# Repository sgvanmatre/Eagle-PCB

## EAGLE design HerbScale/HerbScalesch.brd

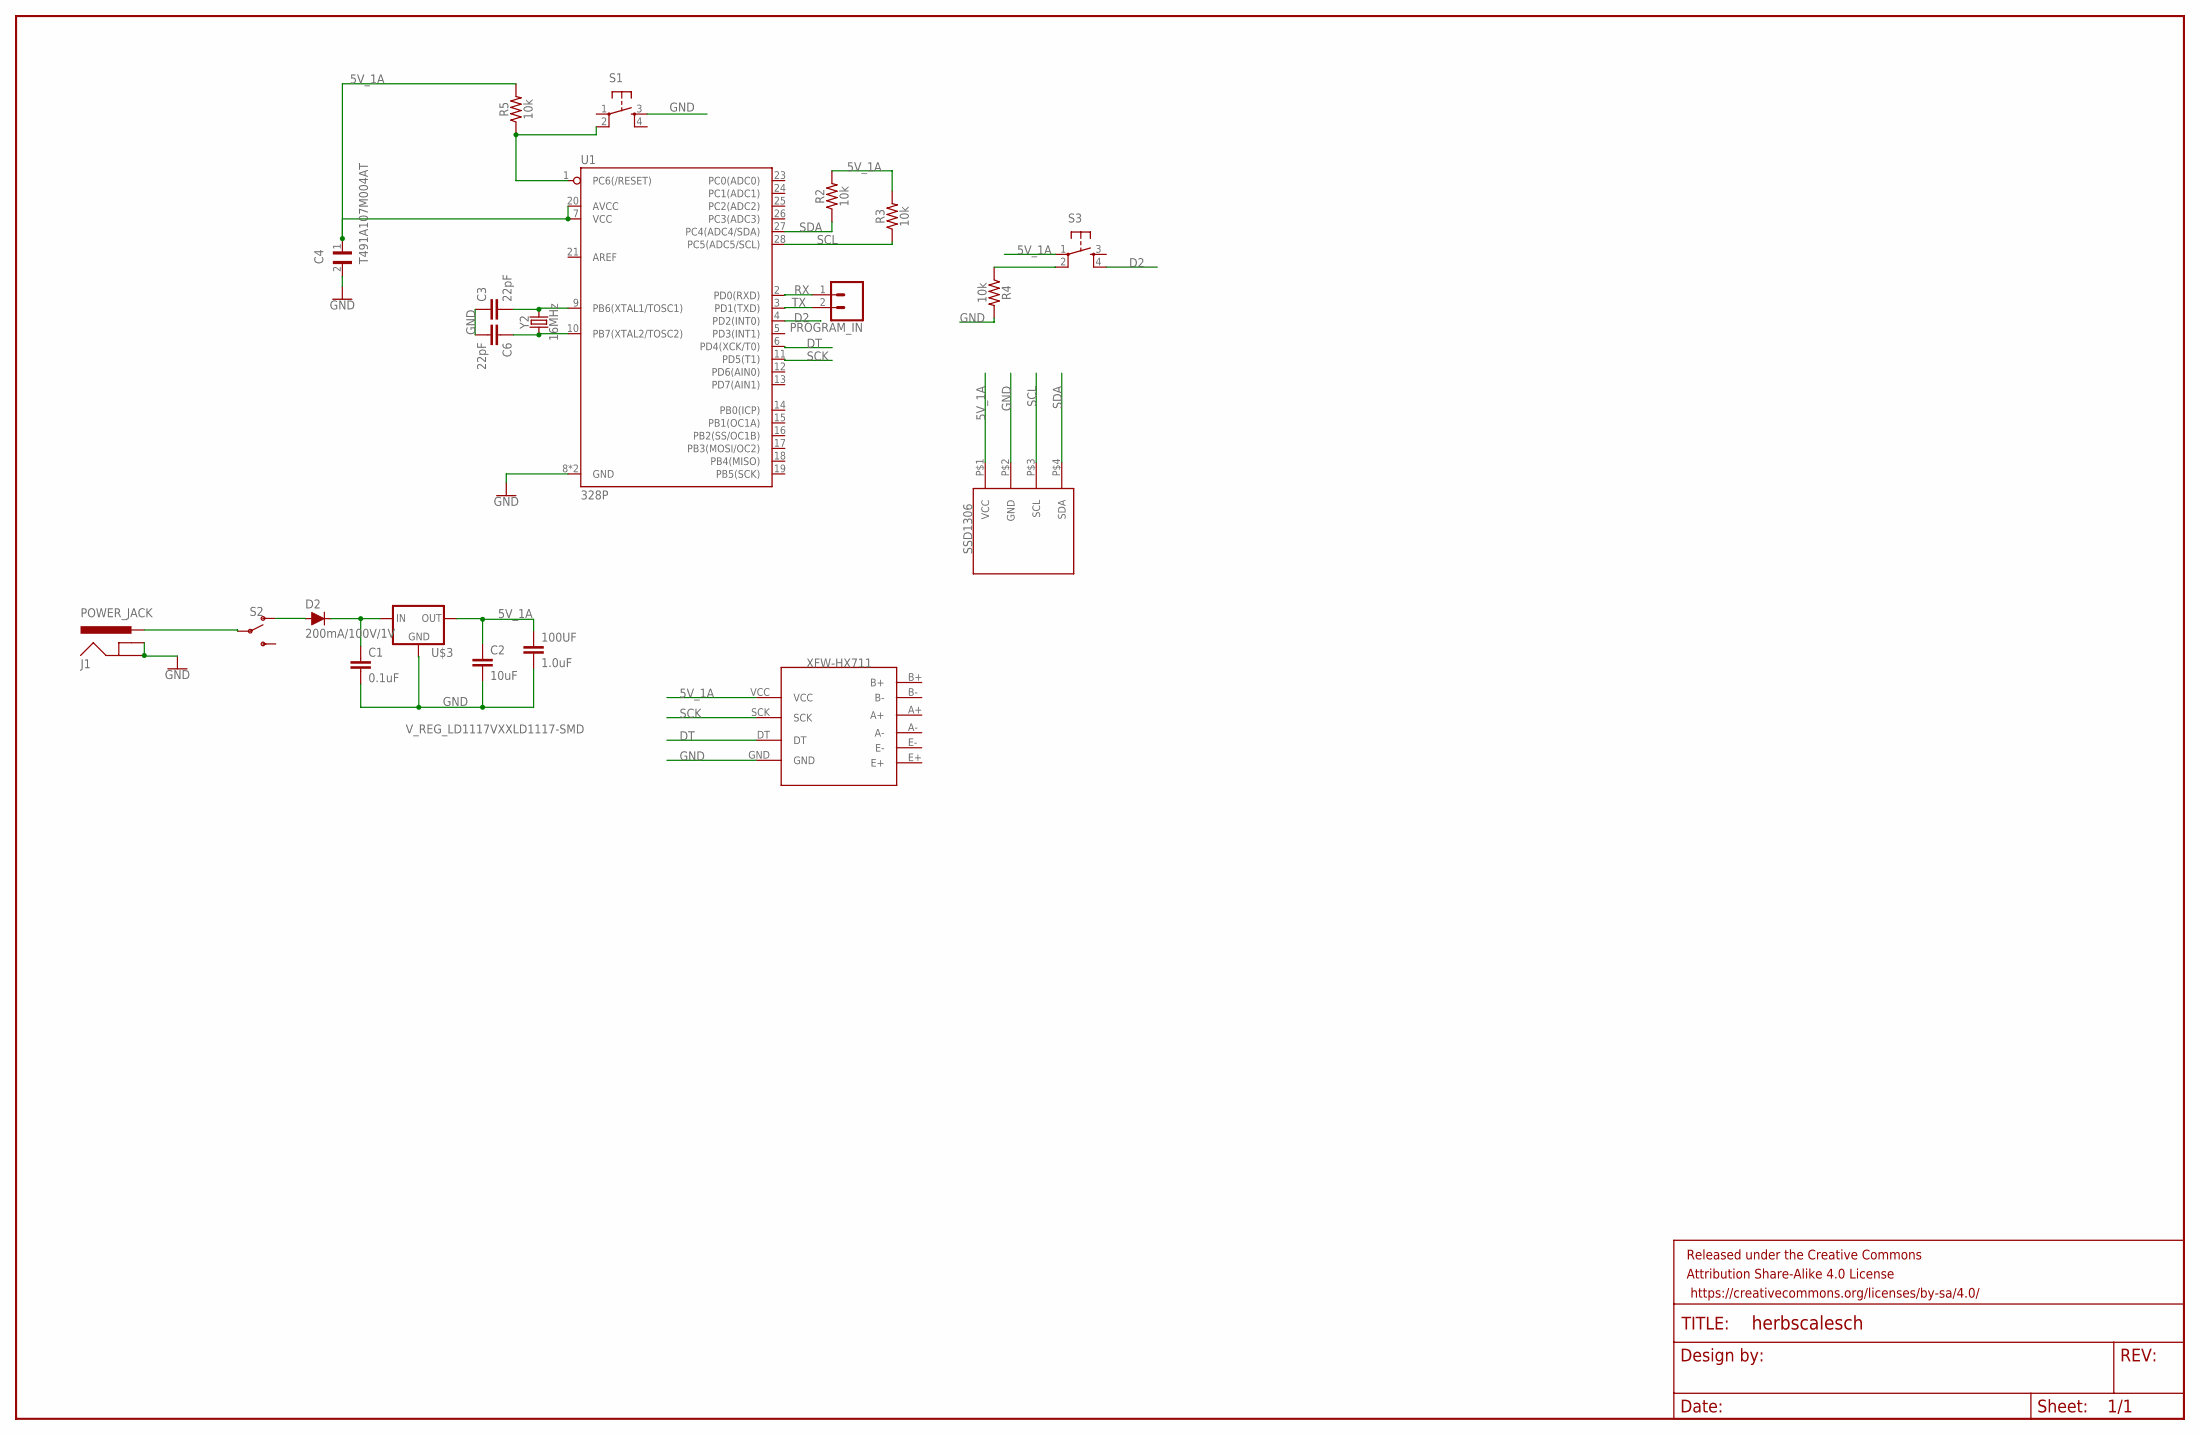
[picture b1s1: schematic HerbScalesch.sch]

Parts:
100UF: 1.0uF; 1206
C1: 0.1uF; 0603
C2: 10uF; 0603
C3, C6: 22pF; CAP-PTH-2.54
C4: T491A107M004AT; CAPC3216X110N
D2: 200mA/100V/1V; DIODE-1N4148
FRAME1: FRAME-LEDGER; CREATIVE_COMMONS
J1: POWER_JACK; POWER_JACK_PTH
PROGRAM_IN: CONN_02; 1X02
R2, R3, R4, R5: 10k; AXIAL-0.3
S1, S3: TAC_SWITCHPTH; TACTILE-PTH
S2: SWITCH-SPDT-PTH-11.6X4.0MM; SWITCH_SPDT_PTH_11.6X4.0MM
U1: 328P; DIP28
U$1: SSD1306
U$2: XFW-HX711
U$3: V_REG_LD1117VXXLD1117-SMD; SOT223
Y2: 16MHz; HC49US

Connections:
5V_1A: 100UF.1, C2.1, C4.1, R2.P$2 (2), R3.P$2 (2), R5.P$2 (2), S3.1, U1.7 (VCC), U1.20 (AVCC), U$1.P$1 (VCC), U$2.VCC, U$3.2 (OUT)
D2: S3.4, U1.4 (PD2(INT0))
DT: U1.6 (PD4(XCK/T0)), U$2.DT
GND: 100UF.2, C1.2, C2.2, C3.1, C4.2, C6.2, J1.GND, J1.GNDBREAK, R4.P$2 (2), S1.3, U1.8 (GND), U1.22 (GND), U$1.P$2 (GND), U$2.GND, U$3.1 (GND)
unnamed: C3.2, U1.9 (PB6(XTAL1/TOSC1)), Y2.2
unnamed: R5.P$1 (1), S1.2, U1.1 (PC6(/RESET))
unnamed: D2.A, S2.1 (O)
unnamed: C1.1, D2.C, U$3.3 (IN)
unnamed: C6.1, U1.10 (PB7(XTAL2/TOSC2)), Y2.1
unnamed: R4.P$1 (1), S3.2
unnamed: J1.PWR, S2.2
RX: PROGRAM_IN.1, U1.2 (PD0(RXD))
SCK: U1.11 (PD5(T1)), U$2.SCK
SCL: R3.P$1 (1), U1.28 (PC5(ADC5/SCL)), U$1.P$3 (SCL)
SDA: R2.P$1 (1), U1.27 (PC4(ADC4/SDA)), U$1.P$4 (SDA)
TX: PROGRAM_IN.2, U1.3 (PD1(TXD))

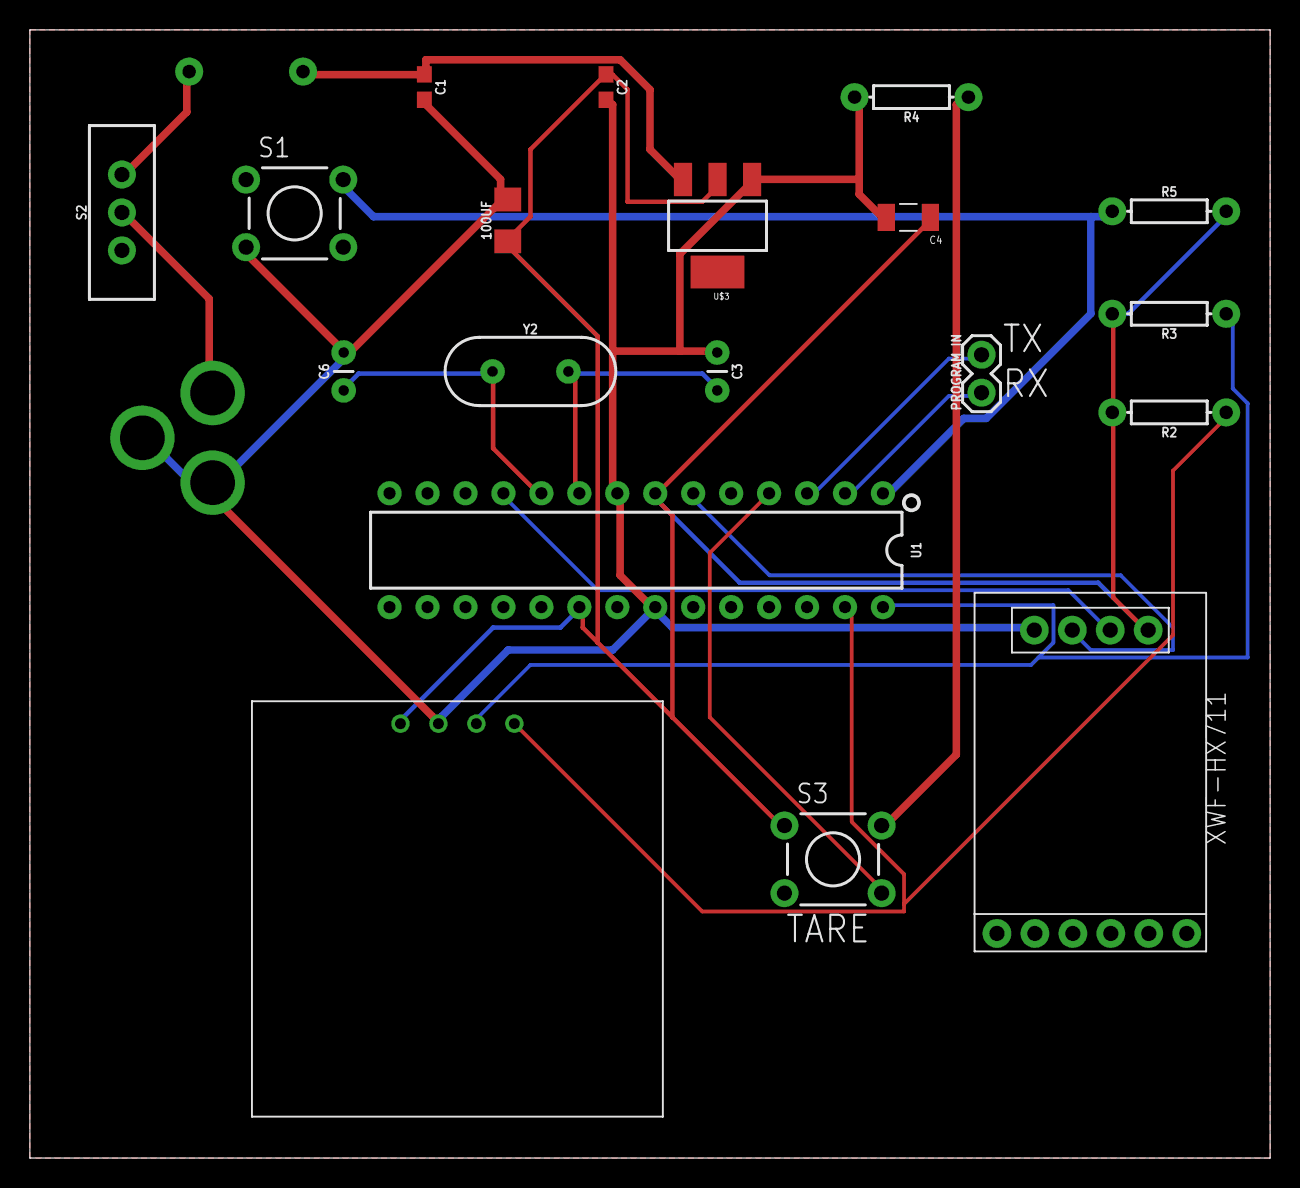
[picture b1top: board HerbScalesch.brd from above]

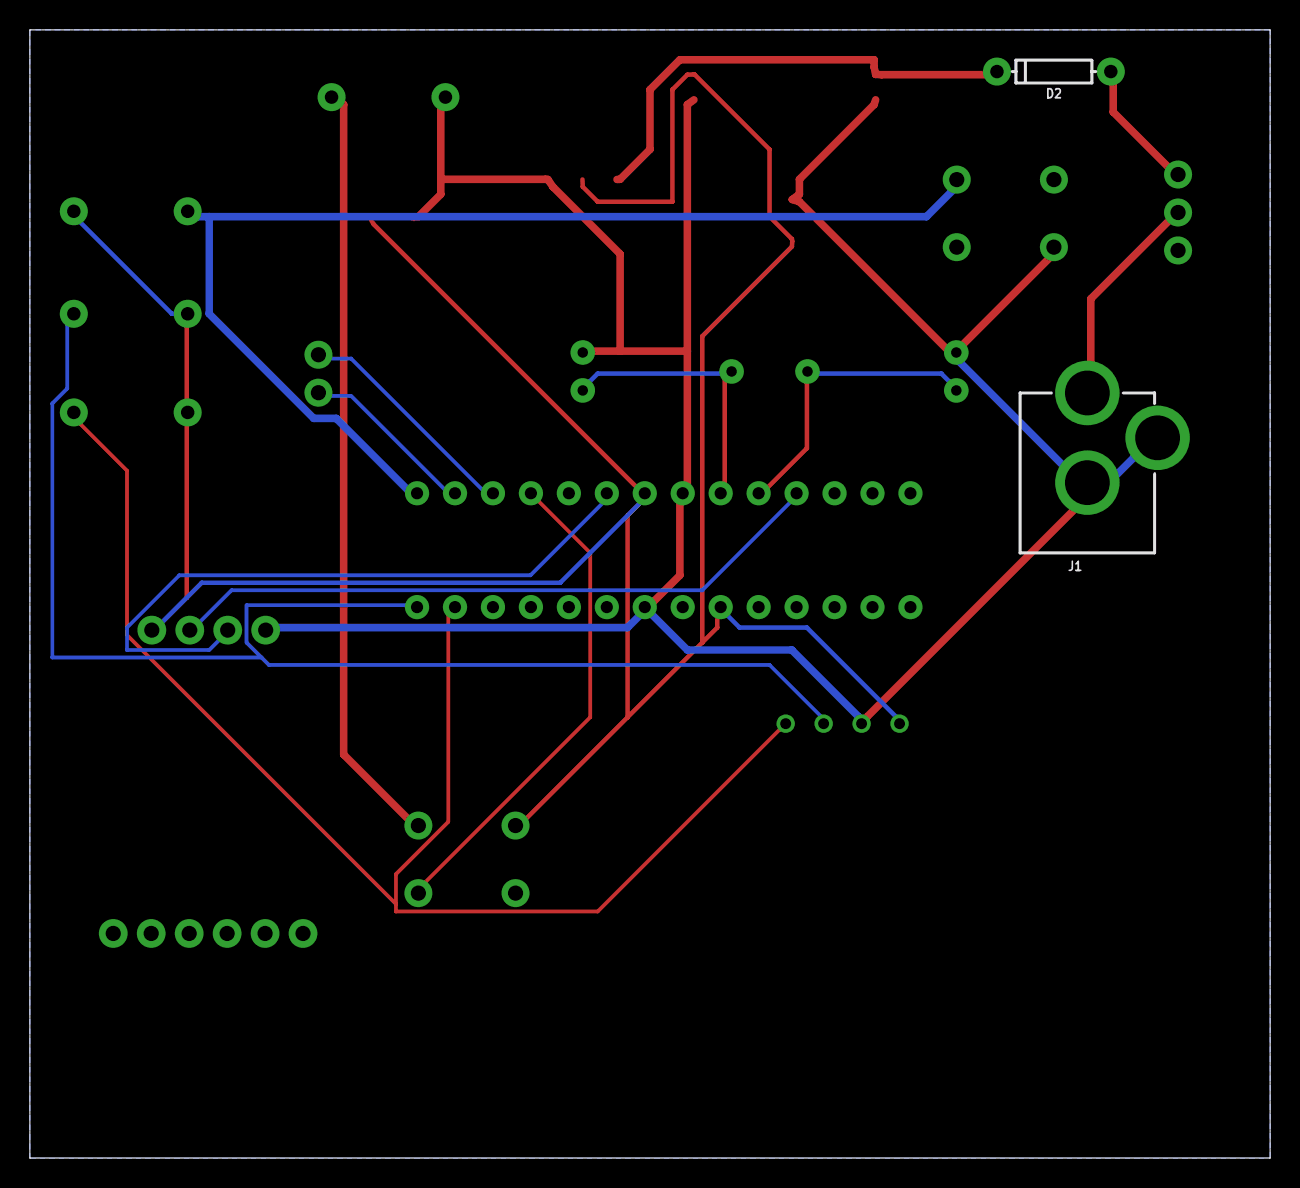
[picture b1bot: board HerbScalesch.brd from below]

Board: 2 copper layers, 83.0 x 75.5 mm, 22 parts (2 on the bottom side), 16 nets.

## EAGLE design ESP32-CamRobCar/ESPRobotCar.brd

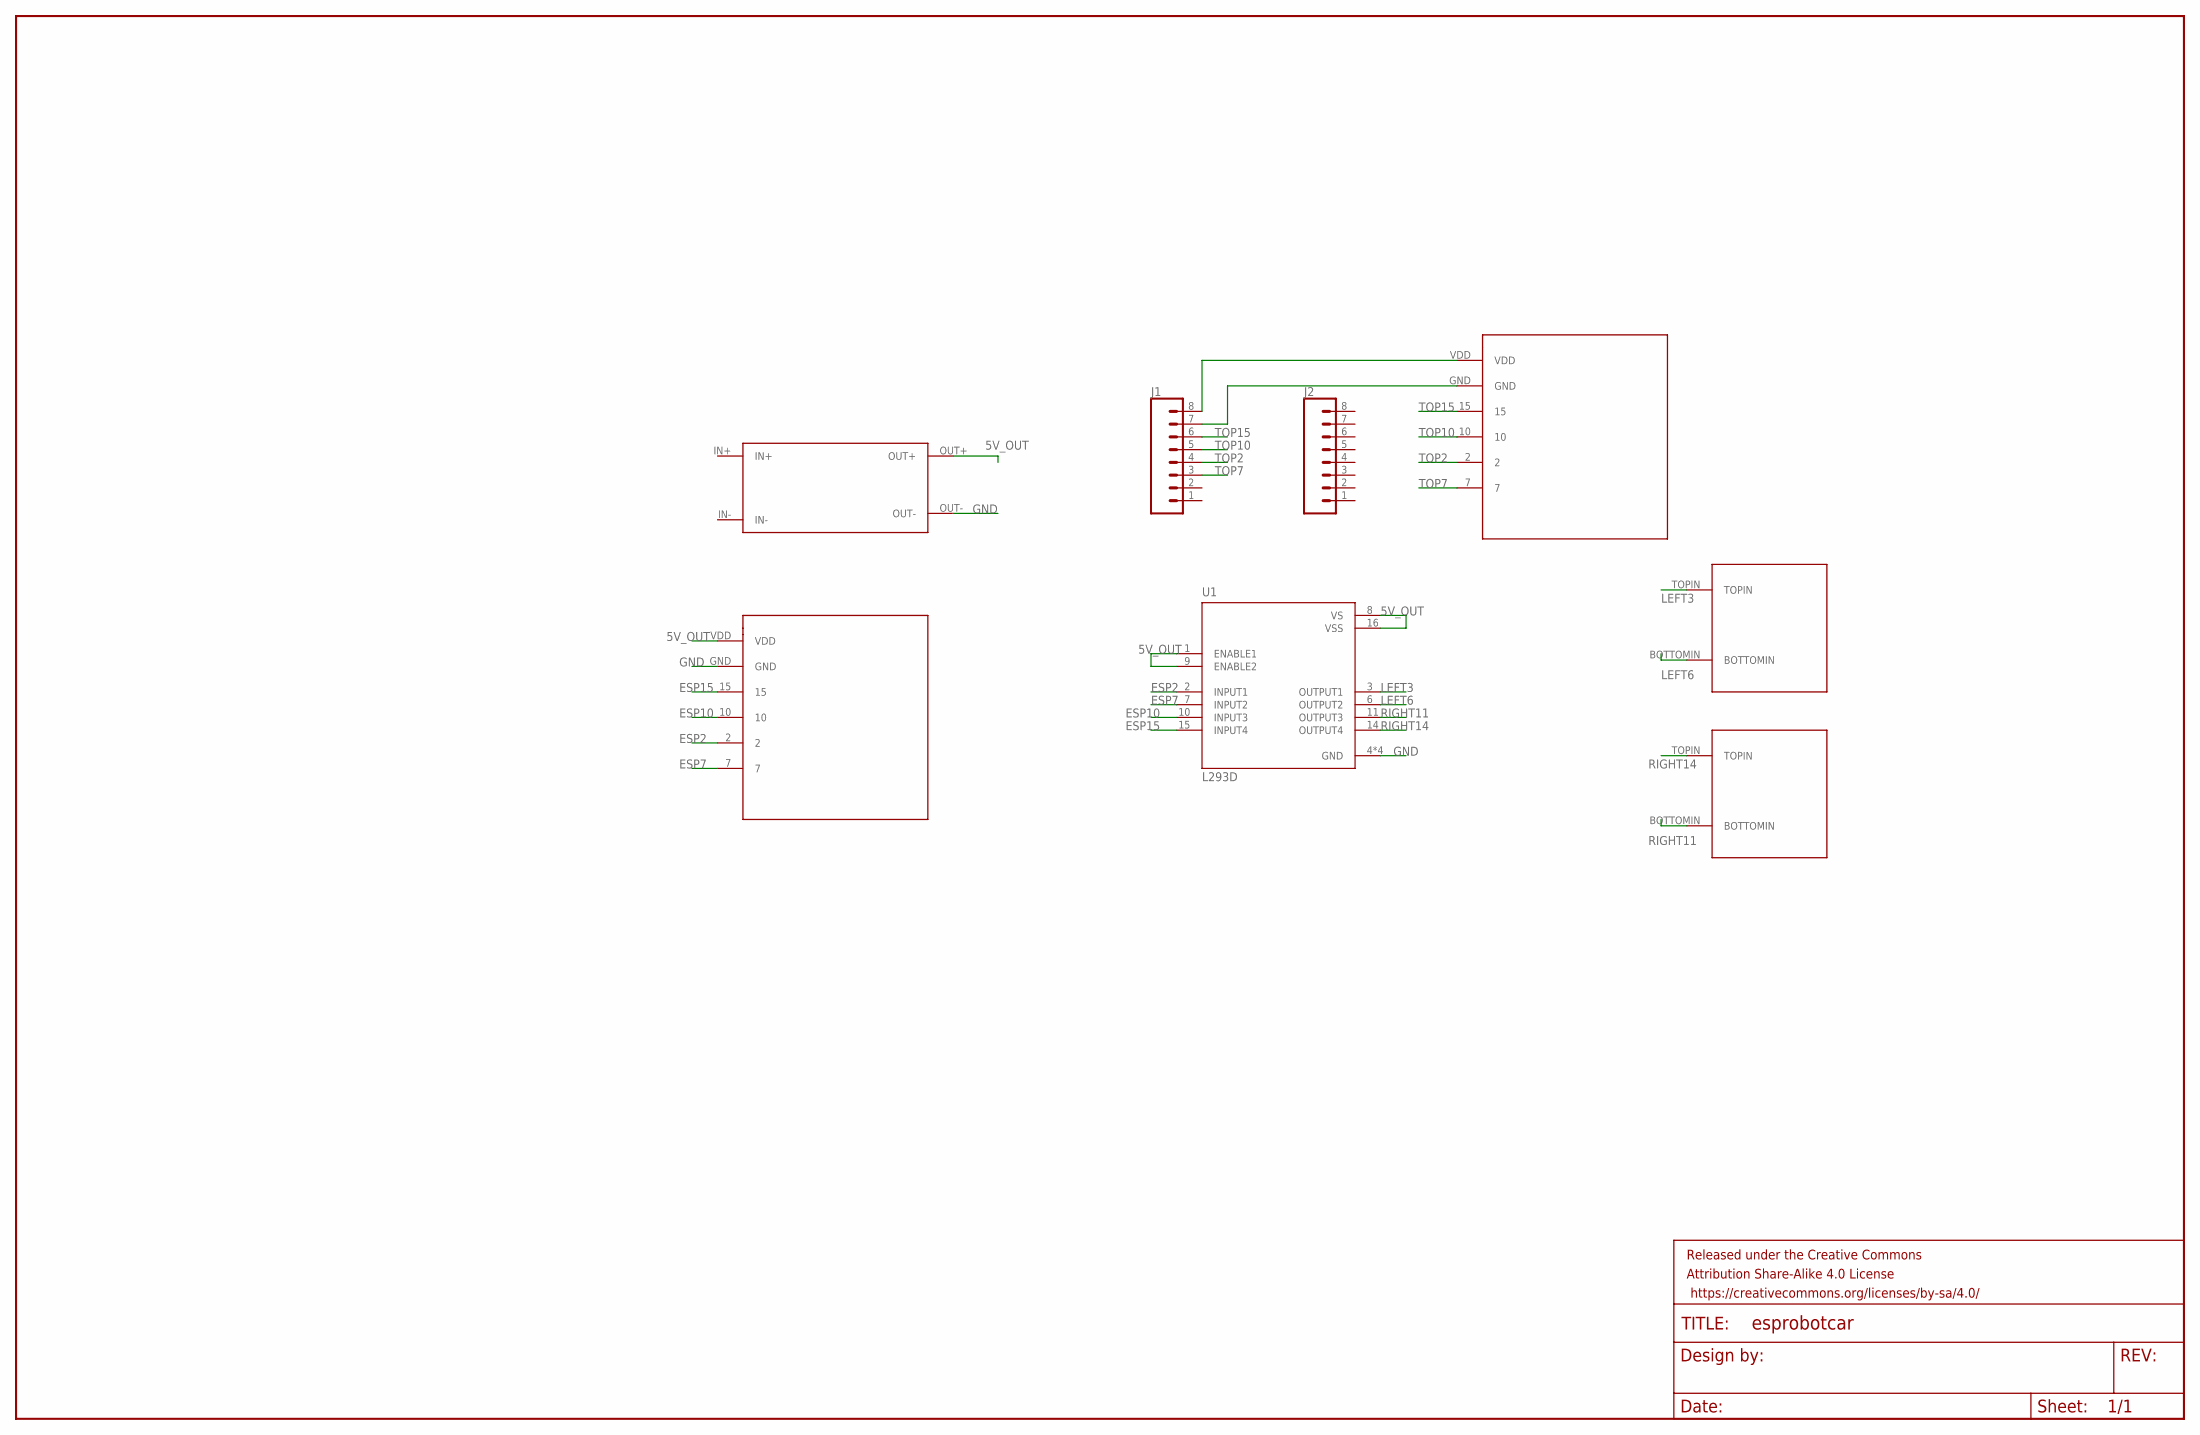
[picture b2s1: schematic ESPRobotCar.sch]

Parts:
FRAME1: FRAME-LEDGER; CREATIVE_COMMONS
J1, J2: CONN_08"; 1X08
U1: L293D; DIP880W50P254L2000H510Q16
U$1: DC_TO_DC; DCTODC
U$2, U$3: MOTORPAD
U$4, U$5: MOTORBREAK

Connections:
5V_OUT: U1.1 (ENABLE1), U1.8 (VS), U1.9 (ENABLE2), U1.16 (VSS), U$1.OUT+, U$4.VDD
ESP2: U1.2 (INPUT1), U$4.2
ESP7: U1.7 (INPUT2), U$4.7
ESP10: U1.10 (INPUT3), U$4.10
ESP15: U1.15 (INPUT4), U$4.15
GND: U1.4 (GND), U1.5 (GND), U1.12 (GND), U1.13 (GND), U$1.OUT-, U$4.GND
LEFT3: U1.3 (OUTPUT1), U$2.TOPIN
LEFT6: U1.6 (OUTPUT2), U$2.BOTTOMIN
unnamed: J1.8, U$5.VDD
unnamed: J1.7, U$5.GND
RIGHT11: U1.11 (OUTPUT3), U$3.BOTTOMIN
RIGHT14: U1.14 (OUTPUT4), U$3.TOPIN
TOP2: J1.4, U$5.2
TOP7: J1.3, U$5.7
TOP10: J1.5, U$5.10
TOP15: J1.6, U$5.15

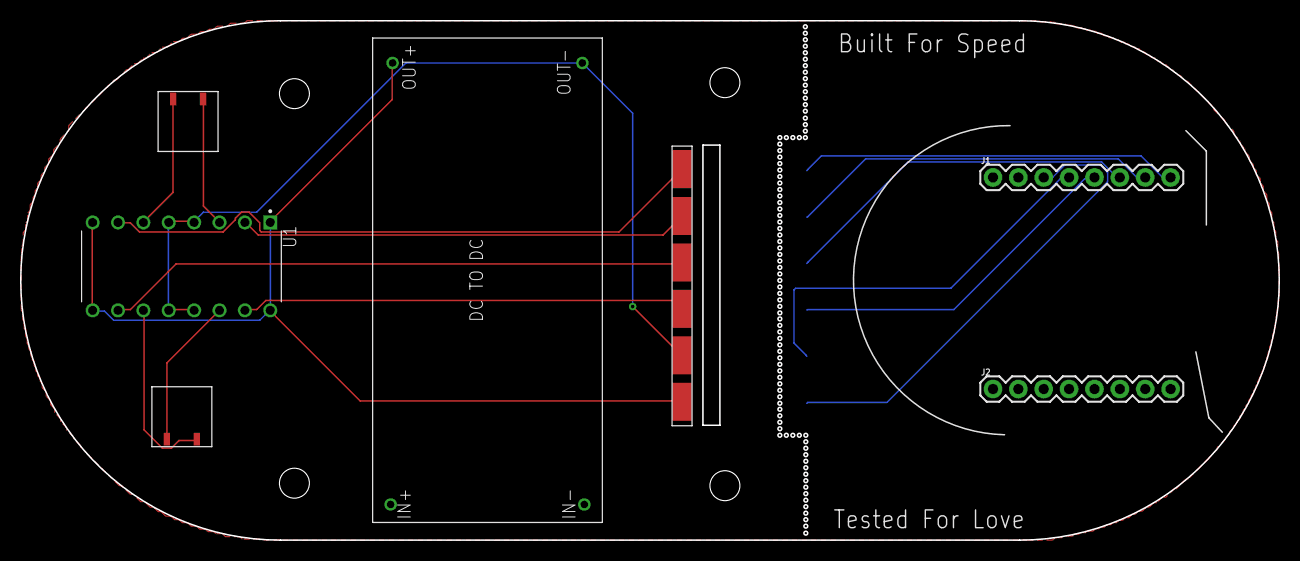
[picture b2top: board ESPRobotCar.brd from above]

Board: 2 copper layers, 126.0 x 52.0 mm, 9 parts (1 on the bottom side), 16 nets.

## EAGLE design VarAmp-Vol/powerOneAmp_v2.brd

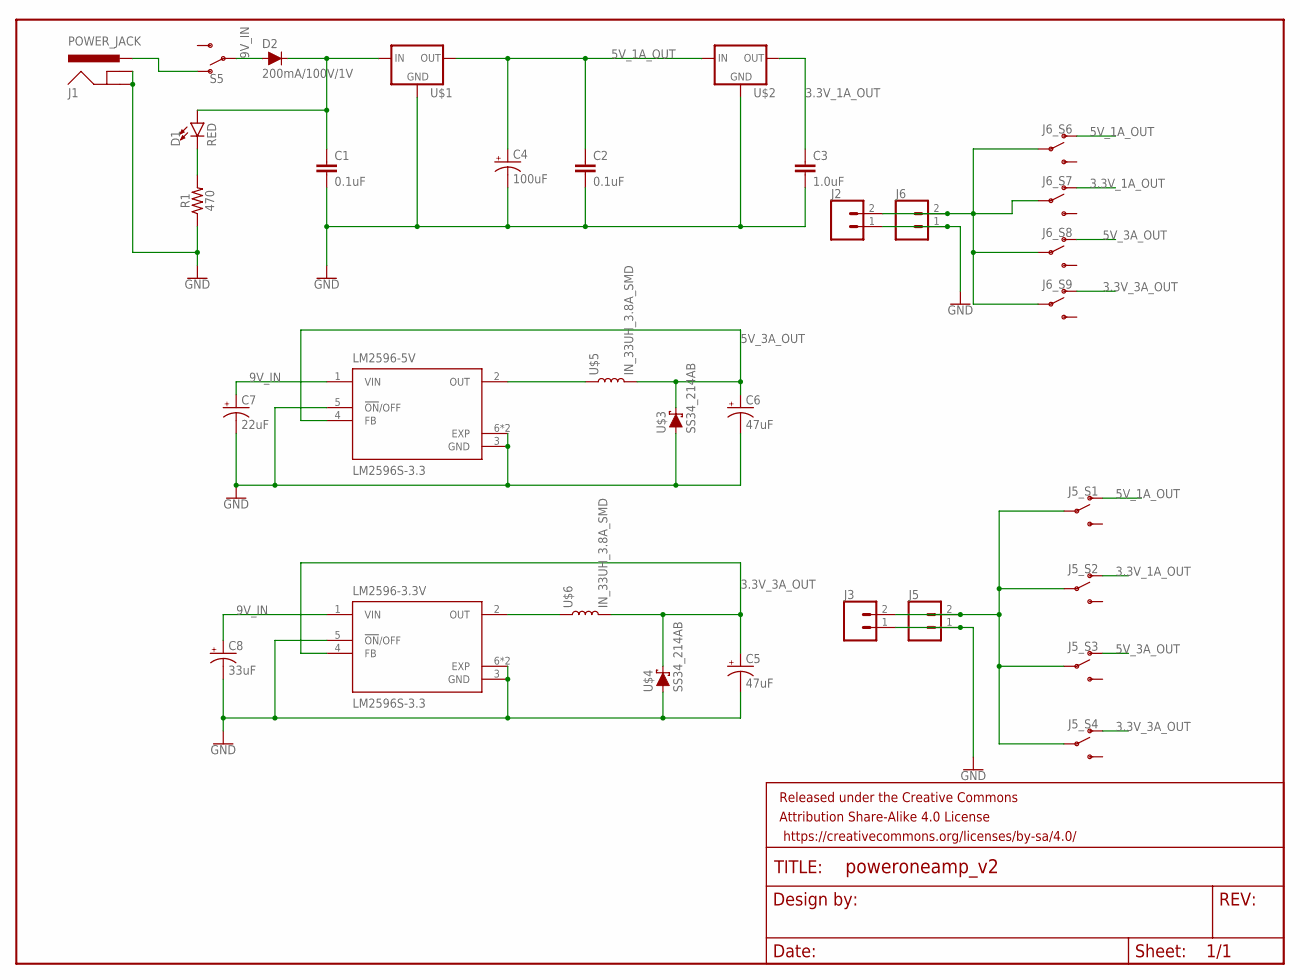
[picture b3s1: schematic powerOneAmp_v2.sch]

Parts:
C1, C2: 0.1uF; 0603
C3: 1.0uF; 0603
C4: 100uF; PANASONIC_D
C5, C6: 47uF; PANASONIC_D
C7: 22uF; PANASONIC_D
C8: 33uF; PANASONIC_D
D1: RED; LED-0603
D2: 200mA/100V/1V; DIODE-1N4148
FRAME1: FRAME-LETTER; CREATIVE_COMMONS
J1: POWER_JACK; POWER_JACK_PTH
J2, J3, J5, J6: CONN_02; 1X02
J5_S1, J5_S2, J5_S3, J5_S4, J6_S6, J6_S7, J6_S8, J6_S9: SWITCH-SPDT-PTH-11.6X4.0MM; SWITCH_SPDT_PTH_11.6X4.0MM
LM2596-3.3V, LM2596-5V: LM2596S-3.3; VREG_LM2596S-3.3
R1: 470; 0603
S5: SWITCH-SPDT-PTH-11.6X4.0MM; SWITCH_SPDT_PTH_11.6X4.0MM
U$1, U$2: V_REG_LD1117VXXLD1117-SMD; SOT223
U$3, U$4: SS34_214AB; SOD-323
U$5, U$6: IN_33UH_3.8A_SMD; INDUCTOR_4X4MM

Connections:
3.3V_1A_OUT: C3.1, J5_S2.1 (O), J6_S7.1 (O), U$2.2 (OUT)
3.3V_3A_OUT: C5.+, J5_S4.1 (O), J6_S9.1 (O), LM2596-3.3V.4 (FB), U$4.C, U$6.P$2 (2); also elsewhere on the board
5V_1A_OUT: C2.1, C4.+, J5_S1.1 (O), J6_S6.1 (O), U$1.2 (OUT), U$2.3 (IN)
5V_3A_OUT: C6.+, J5_S3.1 (O), J6_S8.1 (O), LM2596-5V.4 (FB), U$3.C, U$5.P$2 (2); also elsewhere on the board
9V_IN: C7.+, C8.+, D2.A, LM2596-3.3V.1 (VIN), LM2596-5V.1 (VIN), S5.2; also elsewhere on the board
GND: C1.2, C2.2, C3.2, C4.-, C5.-, C6.-, C7.-, C8.-, J1.GND, J1.GNDBREAK, J2.1, J3.1, J5.1, J6.1, LM2596-3.3V.3 (GND), LM2596-3.3V.5 (!ON!/OFF), LM2596-3.3V.6 (EXP), LM2596-5V.3 (GND), LM2596-5V.5 (!ON!/OFF), LM2596-5V.6 (EXP), R1.1, U$1.1 (GND), U$2.1 (GND), U$3.A, U$4.A; also elsewhere on the board
unnamed: J3.2, J5.2, J5_S1.2, J5_S2.2, J5_S3.2, J5_S4.2
unnamed: D1.C, R1.2
unnamed: C1.1, D1.A, D2.C, U$1.3 (IN)
unnamed: J1.PWR, S5.1 (O)
unnamed 10: LM2596-5V.2 (OUT), U$5.P$1 (1); also elsewhere on the board
unnamed: J2.2, J6.2, J6_S6.2, J6_S7.2, J6_S8.2, J6_S9.2
unnamed 12: LM2596-3.3V.2 (OUT), U$6.P$1 (1); also elsewhere on the board

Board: 2 copper layers, 34 parts (0 on the bottom side), 13 nets, no tracks yet.

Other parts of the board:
3V, 5V: LM2596S-3.3; VREG_LM2596S-3.3

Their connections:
3.3V_3A_OUT: 3V.4; also elsewhere on the board
5V_3A_OUT: 5V.4; also elsewhere on the board
9V_IN: 3V.1, 5V.1; also elsewhere on the board
GND: 3V.3, 3V.5, 3V.6, 3V.7, 5V.3, 5V.5, 5V.6, 5V.7; also elsewhere on the board
unnamed 10: 5V.2; also elsewhere on the board
unnamed 12: 3V.2; also elsewhere on the board

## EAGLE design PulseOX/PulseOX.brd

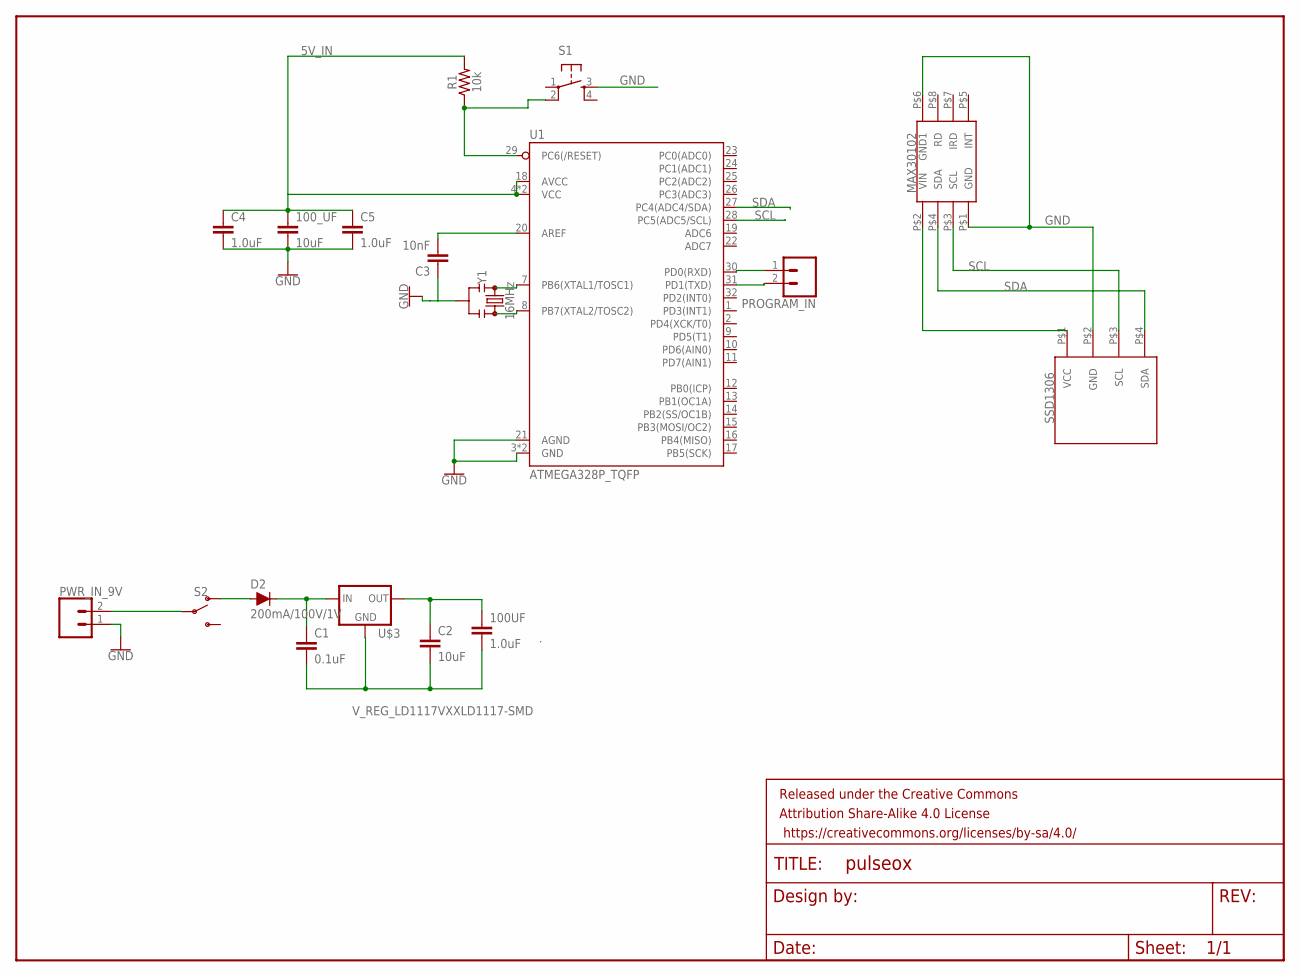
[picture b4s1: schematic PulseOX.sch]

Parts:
100UF: 1.0uF; 1206
100_UF: 10uF; 1206
C1: 0.1uF; 0603
C2: 10uF; 0603
C3: 10nF; 0603
C4, C5: 1.0uF; 0603
D2: 200mA/100V/1V; DIODE-1N4148
FRAME1: FRAME-LETTER; CREATIVE_COMMONS
PROGRAM_IN: CONN_02; 1X02
PWR_IN_9V: CONN_02; 1X02
R1: 10k; 0603
S1: TAC_SWITCHPTH; TACTILE-PTH
S2: SWITCH-SPDT-PTH-11.6X4.0MM; SWITCH_SPDT_PTH_11.6X4.0MM
U1: ATMEGA328P_TQFP; TQFP32-08
U$1: MAX30102
U$2: SSD1306
U$3: V_REG_LD1117VXXLD1117-SMD; SOT223
Y1: 16MHz; RESONATOR-SMD-3.2X1.3

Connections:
5V_IN: 100_UF.1, C4.1, C5.1, R1.2, U1.4 (VCC), U1.6 (VCC), U1.18 (AVCC)
GND: 100_UF.2, C3.1, C4.2, C5.2, PWR_IN_9V.1, S1.3, U1.3 (GND), U1.5 (GND), U1.21 (AGND), U$1.P$1 (GND), U$1.P$6 (GND1), U$2.P$2 (GND), Y1.2
unnamed: U1.7 (PB6(XTAL1/TOSC1)), Y1.1
unnamed: U1.8 (PB7(XTAL2/TOSC2)), Y1.3
unnamed: R1.1, S1.2, U1.29 (PC6(/RESET))
unnamed: D2.A, S2.1 (O)
unnamed: C1.1, D2.C, U$3.3 (IN)
unnamed: U$1.P$2 (VIN), U$2.P$1 (VCC)
unnamed: PROGRAM_IN.1, U1.30 (PD0(RXD))
unnamed: PROGRAM_IN.2, U1.31 (PD1(TXD))
unnamed: PWR_IN_9V.2, S2.2
unnamed: C3.2, U1.20 (AREF)
unnamed: 100UF.2, C1.2, C2.2, U$3.1 (GND)
unnamed: 100UF.1, C2.1, U$3.2 (OUT)
SCL: U1.28 (PC5(ADC5/SCL)), U$1.P$3 (SCL), U$2.P$3 (SCL)
SDA: U1.27 (PC4(ADC4/SDA)), U$1.P$4 (SDA), U$2.P$4 (SDA)

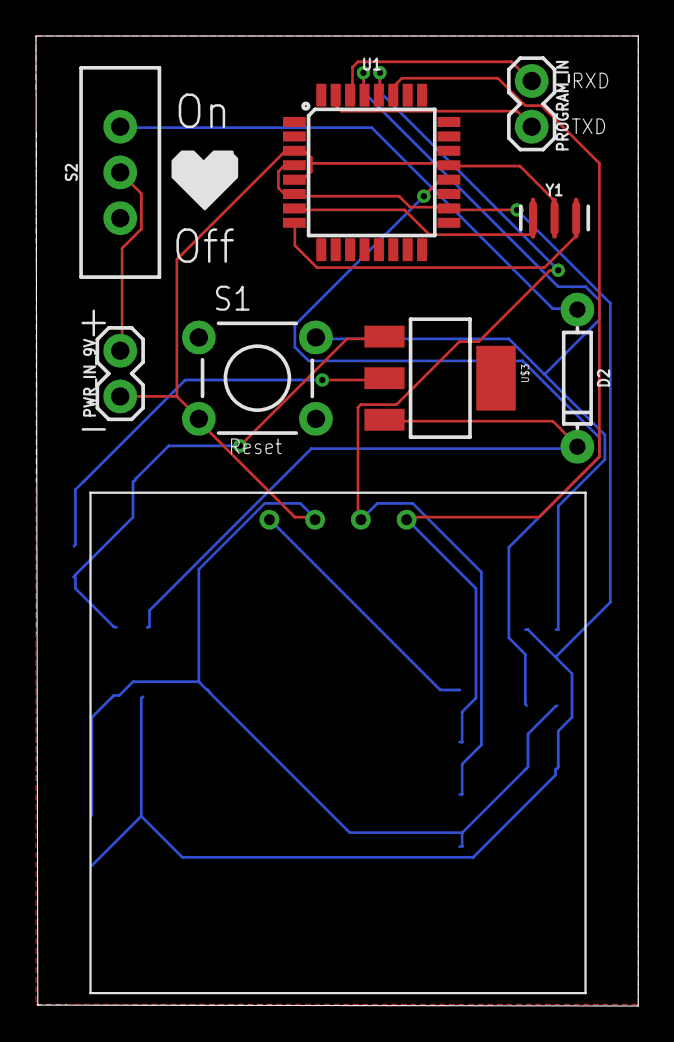
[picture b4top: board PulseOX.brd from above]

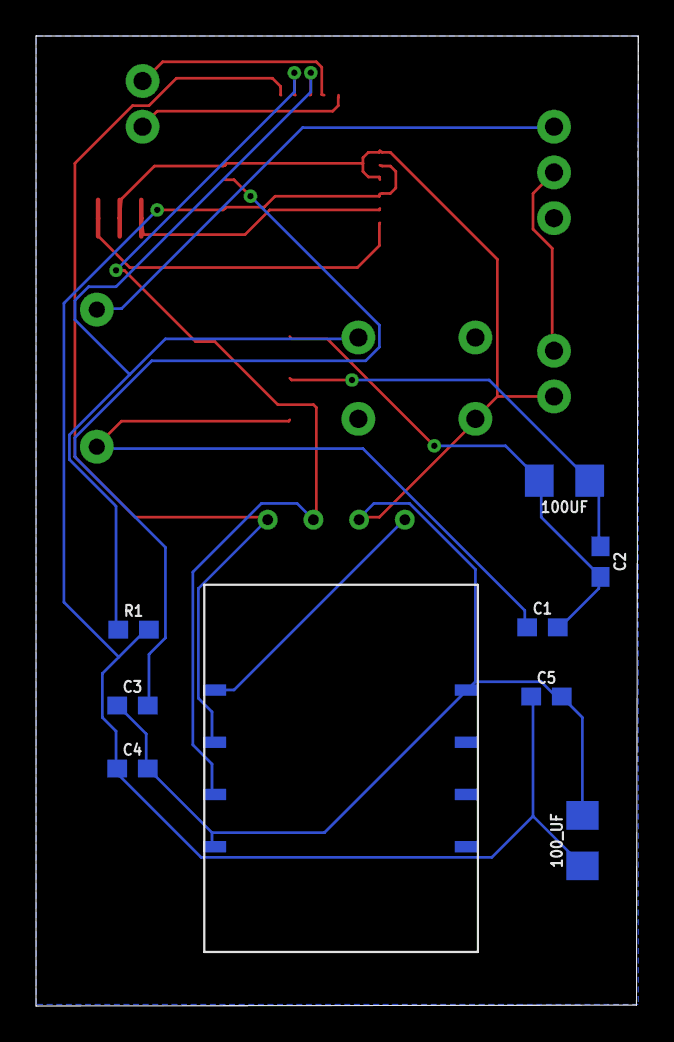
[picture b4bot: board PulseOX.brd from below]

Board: 2 copper layers, 33.5 x 53.9 mm, 19 parts (9 on the bottom side), 16 nets.

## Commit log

2023-11-02 Create 1
2023-11-02 Rename ESPRobotCar.brd to ESP32-CamRobCar/ESPRobotCar.brd
2023-11-02 Rename ESPRobotCar.sch to ESP32-CamRobCar/ESPRobotCar.sch
2023-11-02 Rename HerbScalesch.brd to HerbScale/HerbScalesch.brd
2023-11-02 Rename HerbScalesch.sch to HerbScale/HerbScalesch.sch
2023-11-02 Rename MethaneFlux.brd to MethaneFlux/v1.0/MethaneFlux.brd
2023-11-02 Rename MethaneFlux.sch to MethaneFlux/v1.0/MethaneFlux.sch
2023-11-02 Rename PulseOX.brd to PulseOX/PulseOX.brd
2023-11-02 Rename PulseOX.sch to PulseOX/PulseOX.sch
2023-11-02 Rename powerOneAmp_v2.brd to VarAmp-Vol/powerOneAmp_v2.brd
2023-11-02 Rename powerOneAmp_v2.sch to VarAmp-Vol/powerOneAmp_v2.sch
2023-11-29 Add files via upload
    Added a level shifter for the BME680 for 5V I2C to 3V I2C. Added ferrite bead and 10k resistors to the ADC.
2023-11-29 Rename MethaneFlux/MethaneFlux.brd to MethaneFlux/v1.2.2/MethaneFlux.brd
2023-11-29 Rename MethaneFlux/MethaneFlux.sch to MethaneFlux/v1.2.2/MethaneFlux.sch
2024-02-20 Rename MethaneFlux.sch to MethaneFlux/v2.0/MethaneFlux.sch
2024-02-20 Rename MethaneFlux.brd to MethaneFlux/v2.0/MethaneFlux.brd
2024-05-02 Rename MethaneFlux/MethaneFlux - Copy.sch to MethaneFlux/v2.2/MethaneFlux.sch
2024-05-02 Rename MethaneFlux/MethaneFlux - Copy.brd to MethaneFlux/v2.2/MethaneFlux.brd

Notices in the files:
parts and their libraries:
SparkFun-Aesthetics: Licensing: Creative Commons ShareAlike 4.0 International - https://creativecommons.org/licenses/by-sa/4.0
SparkFun-Aesthetics: Released under the Creative Commons Attribution Share-Alike 4.0 License
SparkFun-Aesthetics: https://creativecommons.org/licenses/by-sa/4.0
